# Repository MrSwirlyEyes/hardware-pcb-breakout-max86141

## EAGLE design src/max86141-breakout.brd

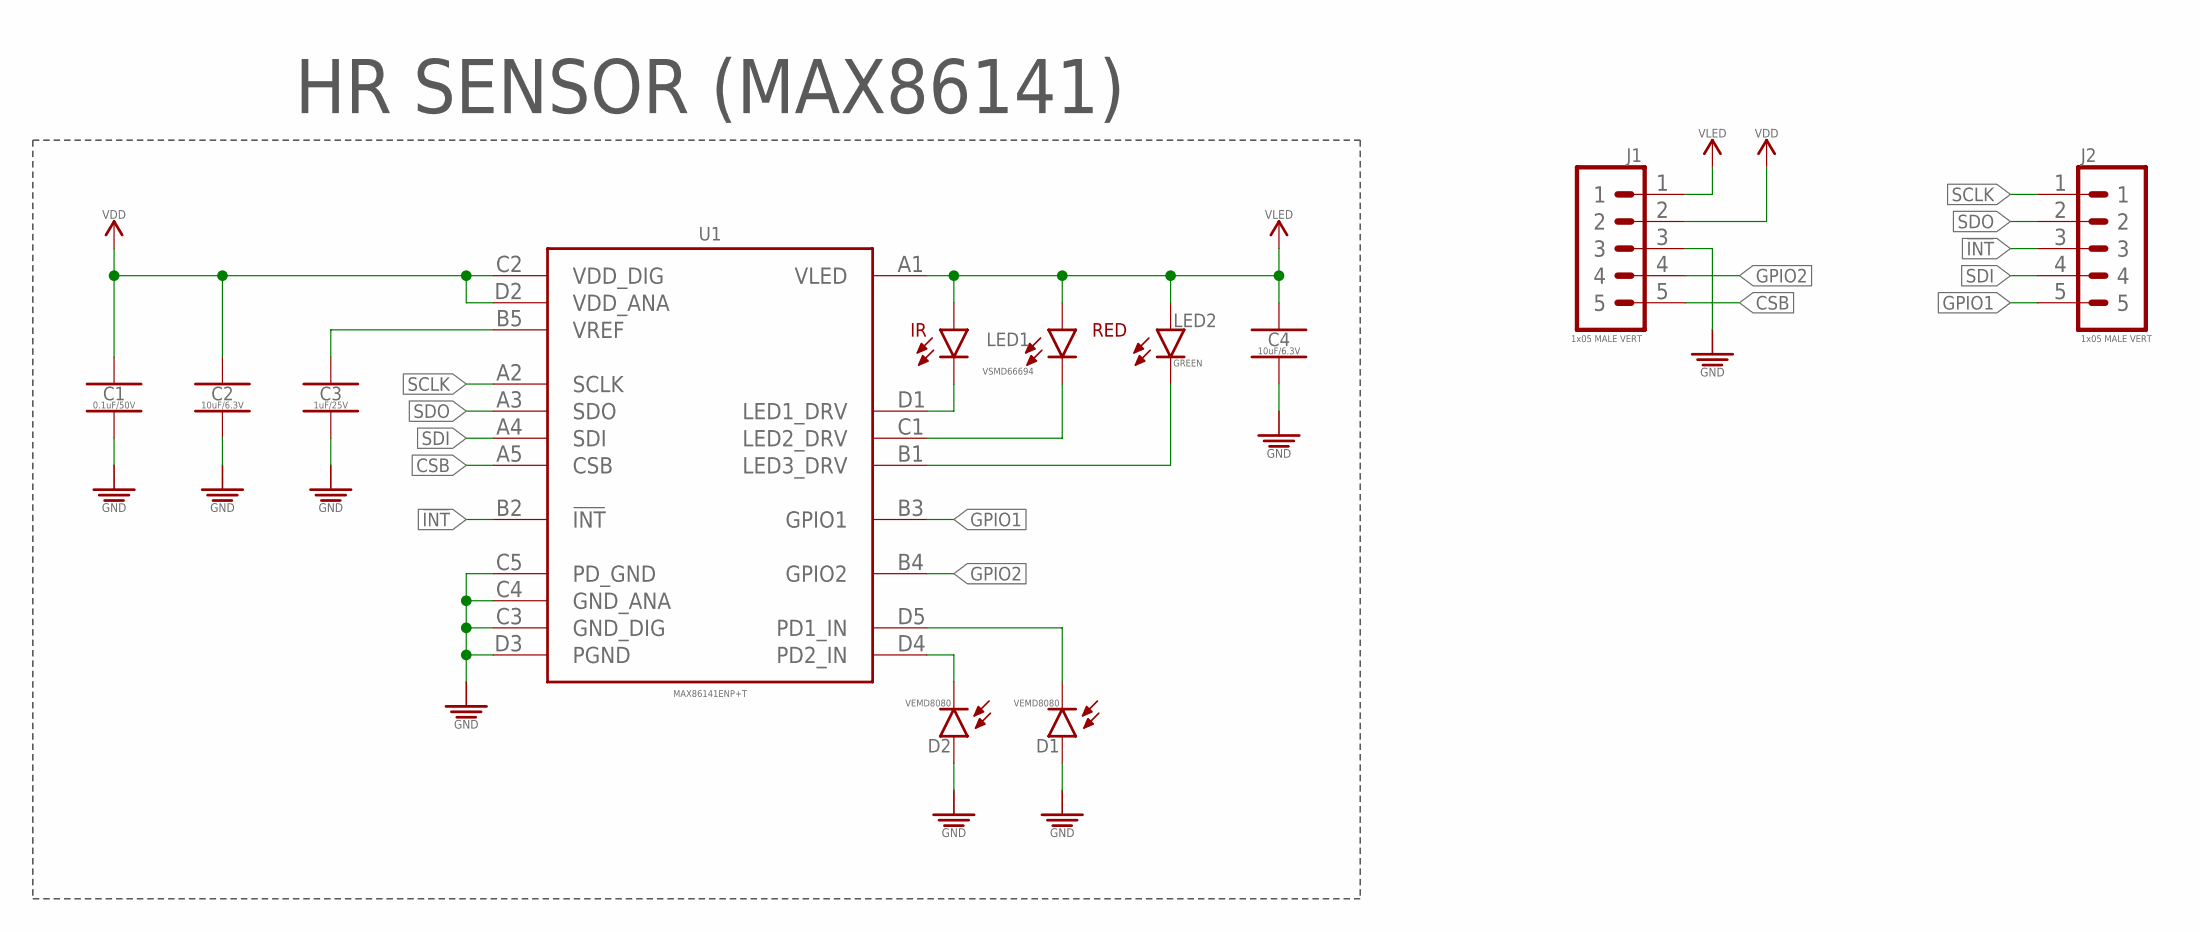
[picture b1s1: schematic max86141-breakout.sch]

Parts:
C1: 0.1uF/50V; CAPC1005X55_SMD-0402
C2, C4: 10uF/6.3V; CAPC1005X55_SMD-0402
C3: 1uF/25V; CAPC1005X55_SMD-0402
D1, D2: VEMD8080; SON131P250X480X53-8N
J1, J2: 1x05 MALE VERT; HDRV5W64P254_1X5_1270X254X838B
LED1: VSMD66694; DIOCAV100P200X200X87-4N
LED2: GREEN; LEDC1005X40_LED-0402
U1: MAX86141ENP+T; BGA20C40P5X4_184X204X100N

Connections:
!INT!: J2.3, U1.B2 (!INT!)
CSB: J1.5, U1.A5 (CSB)
GND: C1.2, C2.2, C3.2, C4.2, D1.1 (A), D1.2 (A), D1.3 (A), D1.4 (A), D1.5 (A), D1.6 (A), D1.7 (A), D2.1 (A), D2.2 (A), D2.3 (A), D2.4 (A), D2.5 (A), D2.6 (A), D2.7 (A), J1.3, U1.C3 (GND_DIG), U1.C4 (GND_ANA), U1.C5 (PD_GND), U1.D3 (PGND)
GPIO1: J2.5, U1.B3 (GPIO1)
GPIO2: J1.4, U1.B4 (GPIO2)
unnamed: D2.8 (K), U1.D4 (PD2_IN)
unnamed: D1.8 (K), U1.D5 (PD1_IN)
unnamed: LED1.1 (K-IR), U1.D1 (LED1_DRV)
unnamed: LED1.3 (K-RED), U1.C1 (LED2_DRV)
unnamed: LED2.K, U1.B1 (LED3_DRV)
unnamed: C3.1, U1.B5 (VREF)
SCLK: J2.1, U1.A2 (SCLK)
SDI: J2.4, U1.A4 (SDI)
SDO: J2.2, U1.A3 (SDO)
VDD: C1.1, C2.1, J1.2, U1.C2 (VDD_DIG), U1.D2 (VDD_ANA)
VLED: C4.1, J1.1, LED1.2 (A-RED), LED1.4 (A-IR), LED2.A, U1.A1 (VLED)

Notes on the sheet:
HR SENSOR (MAX86141)

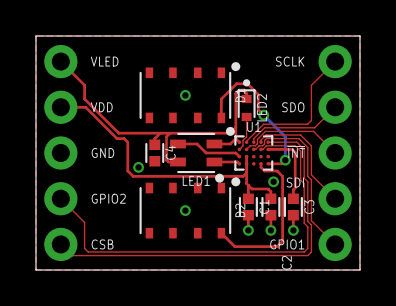
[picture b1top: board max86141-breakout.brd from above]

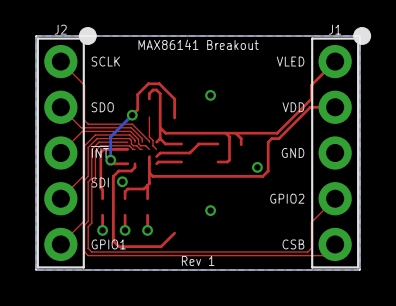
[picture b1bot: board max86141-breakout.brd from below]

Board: 2 copper layers, 18.0 x 13.0 mm, 11 parts (2 on the bottom side), 16 nets.

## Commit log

2021-01-12 [Rev 1] - Initialize repo.
2021-01-17 [Rev 1] - Rearrange components from Chih's feedback. Moved IC out of the way and placed the LEDs symmetrically between the photodiodes.
2021-08-11 Update CAM files.
